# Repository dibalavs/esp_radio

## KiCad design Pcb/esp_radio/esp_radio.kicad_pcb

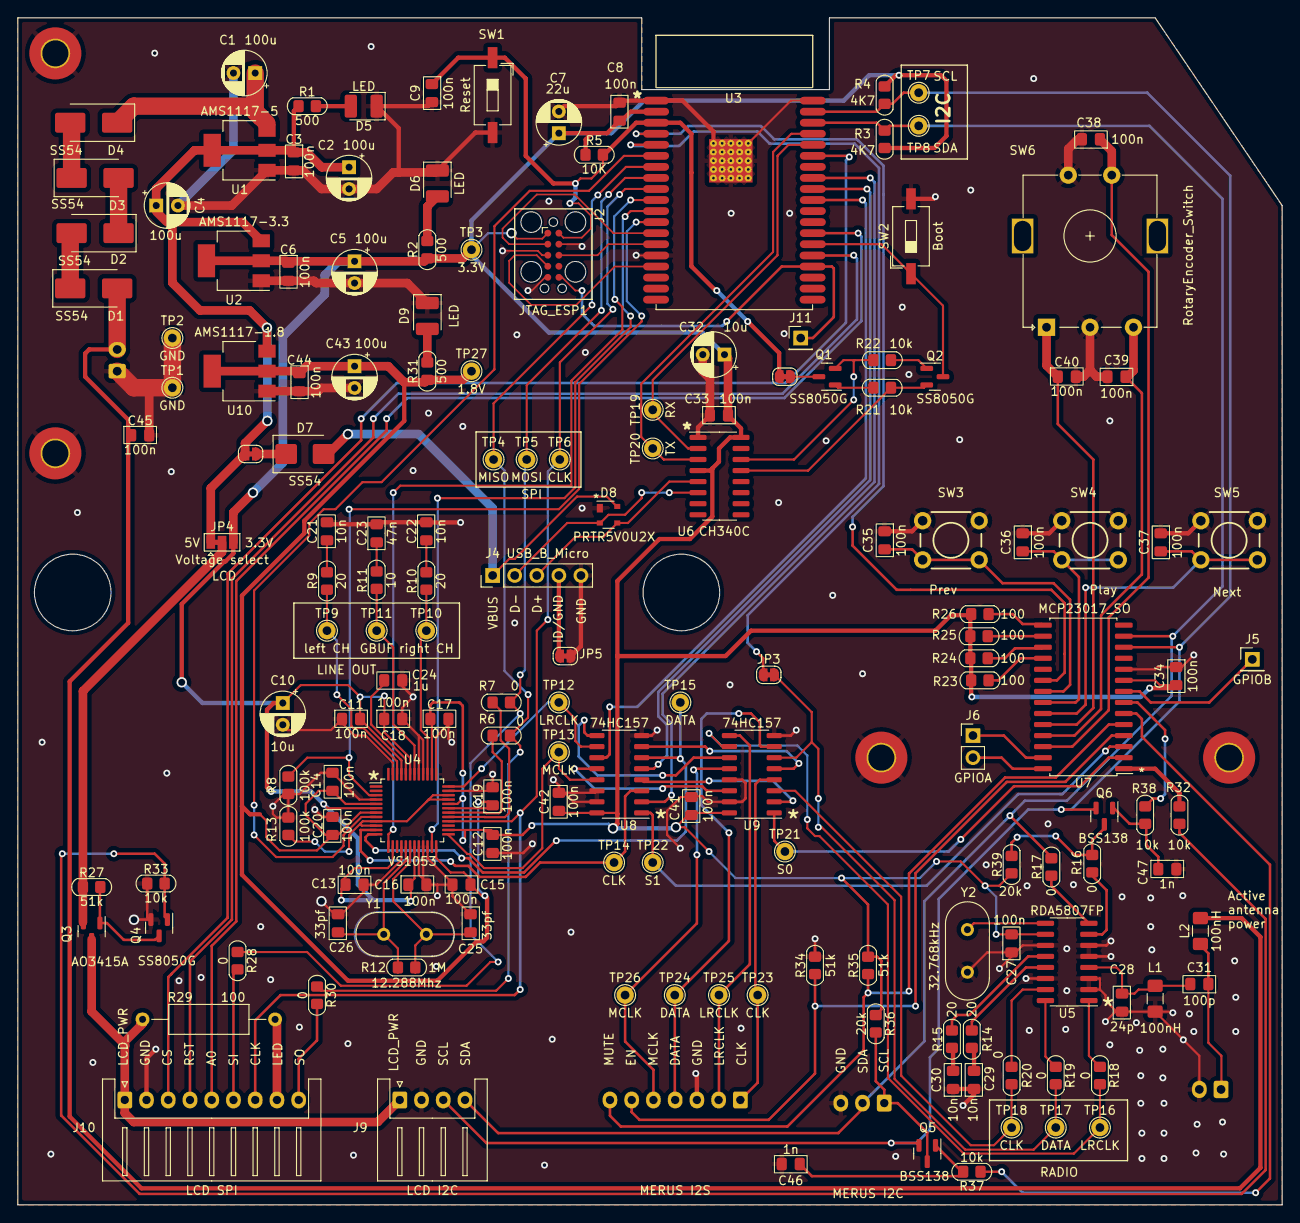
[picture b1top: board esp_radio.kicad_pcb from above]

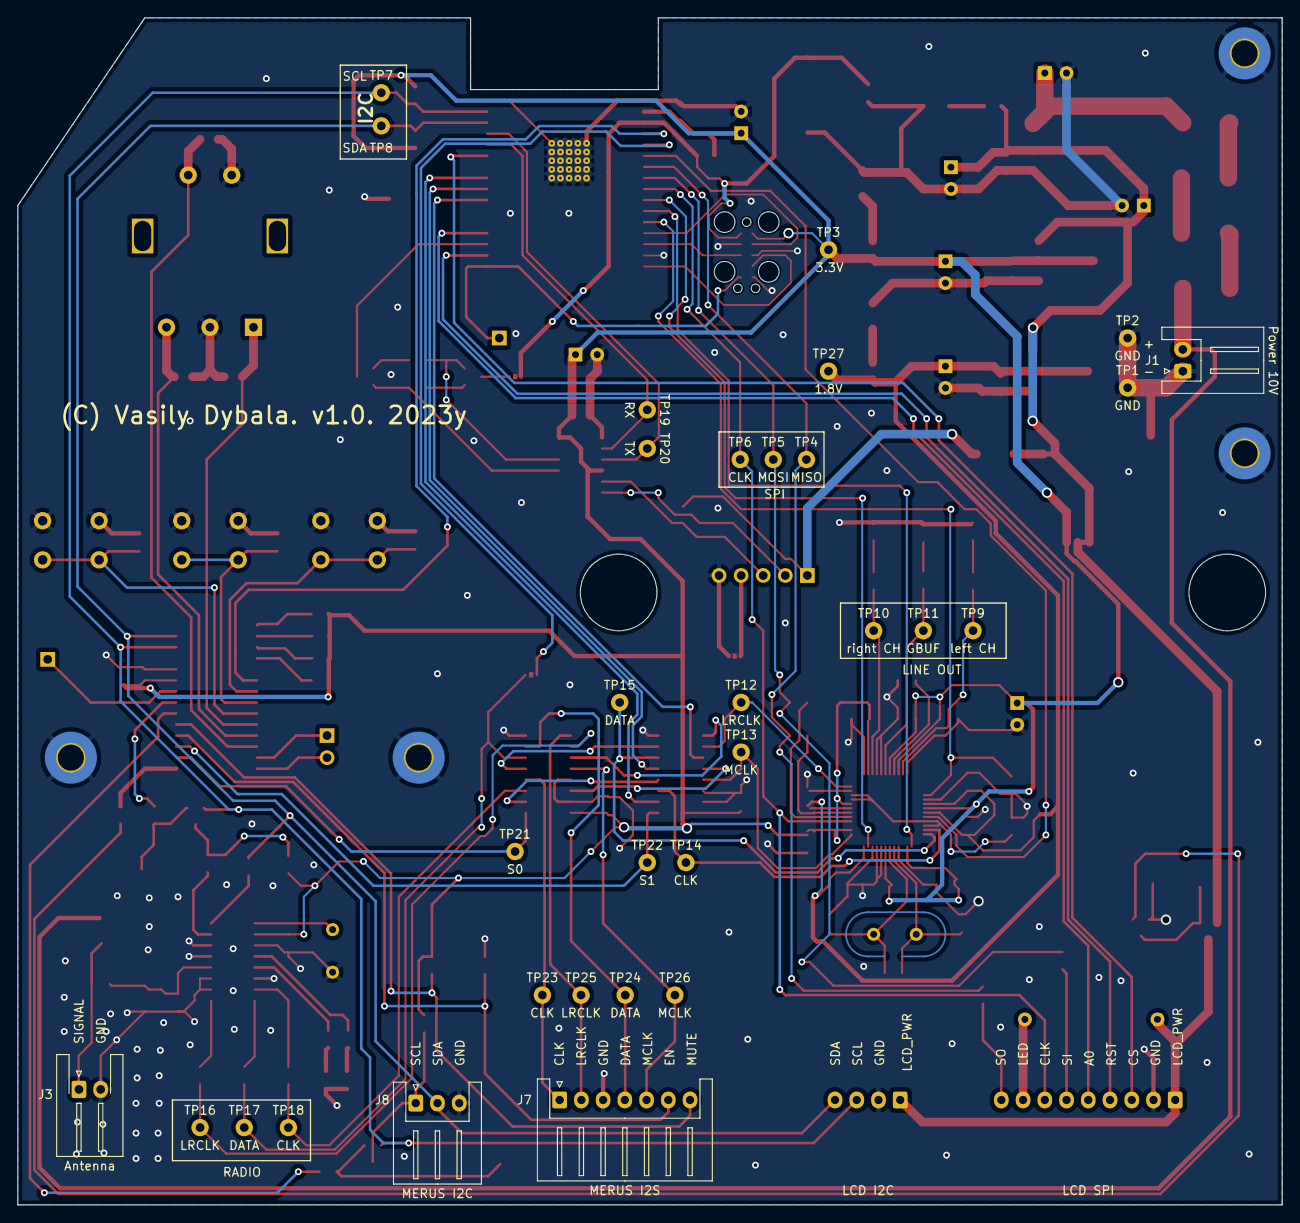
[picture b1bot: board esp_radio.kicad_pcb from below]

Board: 2 copper layers, 145.4 x 136.5 mm, 164 parts (4 on the bottom side), 117 nets.

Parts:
C1, C2, C4, C5, C43: 100u; CP_Radial_D5.0mm_P2.50mm
C3, C6, C8, C9, C11, C12, C13, C14, C15, C16, C17, C18, C19, C20, C27, C33, C34, C35, C36, C37, C38, C39, C40, C41, C42, C44, C45: 100n; C_0805
C7: 22u; CP_Radial_D5.0mm_P2.50mm
C10, C32: 10u; CP_Radial_D5.0mm_P2.50mm
C21, C22, C29, C30: 10n; C_0805
C23: 47n; C_0805
C24: 1u; C_0805
C25, C26: 33pf; C_0805
C28: 24p; C_0805
C31: 100p; C_0805
C46, C47: 1n; C_0805
D1, D2, D3, D4: SS54; D_SMB_Handsoldering
D5, D6, D9: LED; LED_1210_3225Metric_Pad1.42x2.65mm_HandSolder
D7: SS54; D_SMB
D8: PRTR5V0U2X; SOT-143
J1: Power 10V; JST_XH_S2B-XH-A_1x02_P2.50mm_Horizontal
J2: JTAG_ESP1; Tag-Connect_TC2050-IDC-FP_2x05_P1.27mm_Vertical
J3: Antenna; JST_XH_S2B-XH-A-1_1x02_P2.50mm_Horizontal
J4: USB_B_Micro; PinHeader_1x05_P2.54mm_Vertical
J5: GPIOB; PinHeader_1x01_P2.54mm_Vertical
J6: GPIOA; PinHeader_1x02_P2.54mm_Vertical
J7: MERUS I2S; JST_XH_S7B-XH-A_1x07_P2.50mm_Horizontal
J8: MERUS I2C; JST_XH_S3B-XH-A_1x03_P2.50mm_Horizontal
J9: LCD I2C; JST_XH_S4B-XH-A_1x04_P2.50mm_Horizontal
J10: LCD SPI; JST_XH_S9B-XH-A_1x09_P2.50mm_Horizontal
J11: IR; PinHeader_1x01_P2.54mm_Vertical
JP1, JP2, JP3, JP5: SolderJumper_2_Bridged; SolderJumper-2_P1.3mm_Bridged_RoundedPad1.0x1.5mm
JP4: Voltage select; SolderJumper-3_P1.3mm_Bridged12_Pad1.0x1.5mm
L1, L2: 100nH; L_1206_3216Metric_Pad1.42x1.75mm_HandSolder
Q1, Q2, Q4: SS8050G; SOT-23
Q3: AO3415A; SOT-23
Q5, Q6: BSS138; SOT-23
R1, R2, R31: 500; R_0805
R3, R4: 4K7; R_0805
R5: 10K; R_0805
R6, R7, R16, R17, R18, R19, R20, R28, R30: 0; R_0805
R8, R13: 100k; R_0805
R9, R10, R14, R15: 20; R_0805
R11: 10; R_0805
R12: 1M; R_0805
R21, R22, R32, R33, R37, R38: 10k; R_0805
R23, R24, R25, R26: 100; R_0805
R27, R34, R35: 51k; R_0805
R29: 100; R_Axial_DIN0309_L9.0mm_D3.2mm_P15.24mm_Horizontal
R36, R39: 20k; R_0805
SW1: Reset; SW_DIP_SPSTx01_Slide_6.7x4.1mm_W8.61mm_P2.54mm_LowProfile
SW2: Boot; SW_DIP_SPSTx01_Slide_6.7x4.1mm_W8.61mm_P2.54mm_LowProfile
SW3: Prev; SW_PUSH_6mm_H12mm
SW4: Play; SW_PUSH_6mm_H12mm
SW5: Next; SW_PUSH_6mm_H12mm
SW6: RotaryEncoder_Switch; RotaryEncoder_EC16-Switch_Vertical_H20mm
TP1, TP2: GND; TestPoint_THTPad_D2.0mm_Drill1.0mm
TP3: 3.3V; TestPoint_THTPad_D2.0mm_Drill1.0mm
TP4: MISO; TestPoint_THTPad_D2.0mm_Drill1.0mm
TP5: MOSI; TestPoint_THTPad_D2.0mm_Drill1.0mm
TP6, TP14, TP18, TP23: CLK; TestPoint_THTPad_D2.0mm_Drill1.0mm
TP7: SCL; TestPoint_THTPad_D2.0mm_Drill1.0mm
TP8: SDA; TestPoint_THTPad_D2.0mm_Drill1.0mm
TP9: left CH; TestPoint_THTPad_D2.0mm_Drill1.0mm
TP10: right CH; TestPoint_THTPad_D2.0mm_Drill1.0mm
TP11: GBUF; TestPoint_THTPad_D2.0mm_Drill1.0mm
TP12, TP16, TP25: LRCLK; TestPoint_THTPad_D2.0mm_Drill1.0mm
TP13, TP26: MCLK; TestPoint_THTPad_D2.0mm_Drill1.0mm
TP15, TP17, TP24: DATA; TestPoint_THTPad_D2.0mm_Drill1.0mm
TP19: RX; TestPoint_THTPad_D2.0mm_Drill1.0mm
TP20: TX; TestPoint_THTPad_D2.0mm_Drill1.0mm
TP21: S0; TestPoint_THTPad_D2.0mm_Drill1.0mm
TP22: S1; TestPoint_THTPad_D2.0mm_Drill1.0mm
TP27: 1.8V; TestPoint_THTPad_D2.0mm_Drill1.0mm
U1: AMS1117-5; SOT-223-3_TabPin2
U2: AMS1117-3.3; SOT-223-3_TabPin2
U3: ESP32-WROVER_IE; ESP32-WROVER
U4: VS1053; LQFP-48_7x7mm_P0.5mm
U5: RDA5807FP; SOP-16_3.9x9.9mm_P1.27mm
U6: CH340C; SOIC-16_3.9x9.9mm_P1.27mm
U7: MCP23017_SO; SOIC-28W_7.5x17.9mm_P1.27mm
U8, U9: 74HC157; SO-16_3.9x9.9mm_P1.27mm
U10: AMS1117-1.8; SOT-223-3_TabPin2
Y1: 12.288Mhz; Crystal_HC18-U_Vertical
Y2: 32.768kHz; Crystal_HC18-U_Vertical

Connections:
+1V8: C14.2, C15.2, C19.1, C20.1, C43.1, C44.1, R31.1, TP27.1, U4.5 (CVDD), U4.7 (CVDD), U4.24 (CVDD), U4.31 (CVDD), U10.2 (VO)
+3.3V: C5.1, C6.1, C7.1, C8.1, C10.1, C11.2, C12.2, C13.2, C16.1, C17.1, C18.1, C27.2, C32.1, C33.2, C34.2, C41.1, C42.1, J2.1 (VTref), JP4.3 (B), R2.1, R3.1, R4.1, R5.1, R23.1, R24.1, R25.1, R26.1, R35.2, R36.1, R39.1, TP3.1, U2.2 (VO), U3.2 (3V3), U4.6 (IOVDD), U4.14 (IOVDD), U4.19 (IOVDD), U4.26 (RX), U4.32 (~XTEST), U4.38 (AVDD), U4.43 (AVDD), U4.45 (AVDD), U5.10 (VDD), U6.4 (V3), U6.16 (VCC), U7.9 (VDD), U8.16 (VCC), U9.16 (VCC)
+5V: C2.1, C3.1, C4.1, JP1.2 (B), JP4.1 (A), R1.1, U1.2 (VO), U2.3 (VI), U10.3 (VI)
+10V: C45.1, D1.2 (A), J1.2, L2.2
/Audio Decoder/I2S.CLK: TP14.1, U4.11 (I2S_SCLK), U8.3 (1|1)
/Audio Decoder/I2S.DATA: TP15.1, U4.12 (I2S_SDATA), U8.6 (2|1)
/Audio Decoder/I2S.LRCLK: TP12.1, U4.36 (I2S_LROUT), U8.10 (3|1)
/Audio Decoder/I2S.MCLK: TP13.1, U4.25 (I2S_MCLK), U8.13 (4|1)
/Audio Decoder/SPI.CLK: J10.7, TP6.1, U3.9 (IO33), U4.28 (SCLK)
/Audio Decoder/SPI.MISO: R6.1, R30.1, TP4.1, U3.7 (IO35)
/Audio Decoder/SPI.MOSI: R7.1, R28.1, TP5.1, U3.8 (IO32)
/Audio Decoder/VS1053.DREQ: U3.6 (IO34), U4.8 (DREQ)
/Audio Decoder/VS1053.RST: R8.1, U3.12 (IO27), U4.3 (~XRESET)
/Audio Decoder/VS1053.XCS: U3.11 (IO26), U4.23 (XCS)
/Audio Decoder/VS1053.XDCS: U3.10 (IO25), U4.13 (~XDCS)
/ESP_board/FM_ST_INT: JP3.1 (A), U3.5 (IO39)
/ESP_board/I2C.SCL: J9.3, Q5.2 (S), Q6.2 (S), R4.2, TP7.1, U3.37 (IO23), U7.12 (SCK)
/ESP_board/I2C.SDA: J8.2, J9.4, R3.2, R17.1, TP8.1, U3.36 (IO22), U7.13 (SDA)
/ESP_board/I2S0.CLK: U3.31 (IO19), U8.2 (1|0)
/ESP_board/I2S0.DATA: U3.30 (IO18), U8.5 (2|0)
/ESP_board/I2S0.LRCLK: U3.29 (IO5), U8.11 (3|0)
/ESP_board/JTAG.RESET: C9.1, J2.10 (~RESET), JP2.1 (A), R5.2, SW1.1, U3.3 (EN)
/ESP_board/JTAG.TCK: J2.4 (SWDCLK/TCK), U3.16 (TCK)
/ESP_board/JTAG.TDI: J2.8 (NC/TDI), U3.14 (TDI)
/ESP_board/JTAG.TDO: J2.6 (SWO/TDO), J11.1, U3.23 (TDO)
/ESP_board/JTAG.TMS: J2.2 (SWDIO/TMS), U3.13 (TMS)
/ESP_board/LCD.A0: J10.5, U3.26 (IO4)
/ESP_board/LCD.CS: J10.3, U3.33 (IO21)
/ESP_board/LCD.RST: J10.4, U3.24 (IO2)
/ESP_board/UART.BOOT: Q2.3 (C), SW2.1, U3.25 (IO0)
/ESP_board/UART.EN: JP2.2 (B), Q1.3 (C)
/ESP_board/UART.RX: TP19.1, U3.34 (RXD0), U6.2 (TXD)
/ESP_board/UART.TX: TP20.1, U3.35 (TXD0), U6.3 (RXD)
/FM Radio/FmChipSelect: R38.1, U7.7 (GPB6)
/FM Radio/I2S.CLK: R20.2, TP18.1, U9.3 (1|1)
/FM Radio/I2S.DATA: JP3.2 (B), R19.2, TP17.1, U9.6 (2|1)
/FM Radio/I2S.LRCLK: R18.2, TP16.1, U9.10 (3|1)
/I2S Switch/74HC.S0: TP21.1, U7.2 (GPB1), U9.1 (S)
/I2S Switch/74HC.S1: TP22.1, U7.3 (GPB2), U8.1 (S)
/I2S Switch/I2SOUT.CLK: J7.1, TP23.1, U9.4 (1Y)
/I2S Switch/I2SOUT.DATA: J7.4, TP24.1, U9.7 (2Y)
/I2S Switch/I2SOUT.LRCLK: J7.2, TP25.1, U9.9 (3Y)
/I2S Switch/I2SOUT.MCLK: J7.5, TP26.1, U9.12 (4Y)
/IO Expander/INT_EXPANDER: U3.4 (IO36), U7.20 (INTA)
/IO Expander/MERUS.EN: J7.6, R34.1, U7.4 (GPB3)
/IO Expander/MERUS.MUTE: J7.7, R35.1, U7.5 (GPB4)
/IO Expander/MerusChipSelect: R37.1, U7.6 (GPB5)
/LCD screen/LCD.LED: J10.8, R29.2
/LCD screen/LCD_POWER: R32.1, U7.1 (GPB0)
/LCD screen/LCD_PWR: J9.1, J10.1, Q3.3 (D), R29.1
/UART/USB_DN: D8.2 (I/O1), J4.2 (D-), U6.6 (UD-)
/UART/USB_DP: D8.3 (I/O2), J4.3 (D+), U6.5 (UD+)
GND: C1.2, C2.2, C3.2, C4.2, C5.2, C6.2, C7.2, C8.2, C9.2, C10.2, C11.1, C12.1, C13.1, C14.1, C15.1, C16.2, C17.2, C18.2, C19.2, C20.2, C21.2, C22.2, C23.2, C24.1, C25.1, C26.2, C27.1, C28.1, C29.1, C30.1, C32.2, C33.1, C34.1, C35.1, C36.1, C37.1, C38.2, C39.2, C40.2, C41.2, C42.2, C43.2, C44.2, C45.2, C46.2, C47.2, D5.1 (K), D6.1 (K), D8.1 (GND), D9.1 (K), J1.1, J2.3 (GND), J2.5 (GND), J2.9 (GNDDetect), J3.2, J4.5 (GND), J7.3, J8.3, J9.2, J10.2, JP5.1 (A), L1.2, Q4.2 (E), R8.2, R13.1, R33.1, R34.2, SW1.2, SW2.2, SW3.2, SW4.2, SW5.2, SW6.C, SW6.S1, TP1.1, TP2.1, U1.1 (GND), U2.1 (GND), U3.1 (GND), U3.15 (GND), U3.38 (GND), U3.39 (GND), U4.4 (DGND), U4.16 (DGND), U4.20 (DGND), U4.21 (DGND), U4.22 (DGND), U4.35 (DGND), U4.37 (AGND), U4.40 (AGND), U4.41 (AGND), U4.47 (AGND), U5.2 (GND), U5.3 (RF_GND), U5.5 (GND), U5.6 (GND), U5.11 (GND), U5.14 (GND), U6.1 (GND), U7.10 (VSS), U8.8 (GND), U8.14 (4|0), U8.15 (~E), U9.8 (GND), U9.13 (4|1), U9.15 (~E), U10.1 (GND), Y2.1
unnamed: C21.1, R9.2
unnamed: C22.1, R10.2
unnamed: C23.1, R11.2
unnamed: C29.2, R14.2
unnamed: C30.2, R15.2
unnamed: D1.1 (K), D2.2 (A)
unnamed: D2.1 (K), D3.2 (A)
unnamed: D3.1 (K), D4.2 (A)
unnamed: C1.1, D4.1 (K), U1.3 (VI)
unnamed: D5.2 (A), R1.2
unnamed: D6.2 (A), R2.2
unnamed: D7.2 (A), D8.4 (VCC), J4.1 (VBUS)
unnamed: D9.2 (A), R31.2
unnamed: C31.1, J3.1, L2.1
unnamed: J4.4 (ID), JP5.2 (B)
unnamed: J5.1, U7.8 (GPB7)
unnamed: J6.1, U7.27 (GPA6)
unnamed: J6.2, U7.28 (GPA7)
unnamed: J8.1, Q5.3 (D), R36.2
unnamed: J10.6, R28.2
unnamed: J10.9, R30.2
unnamed: JP4.2 (C), Q3.2 (S), R27.1
unnamed: Q1.1 (B), R21.2
unnamed: Q1.2 (E), R22.1, U6.14 (~RTS)
unnamed: Q2.1 (B), R22.2
unnamed: Q2.2 (E), R21.1, U6.13 (~DTR)
unnamed: Q3.1 (G), Q4.3 (C), R27.2
unnamed: Q4.1 (B), R32.2, R33.2
unnamed: C46.1, Q5.1 (G), R37.2
unnamed: Q6.3 (D), R16.1, R39.2
unnamed: C47.1, Q6.1 (G), R38.2
unnamed: R11.1, TP11.1, U4.42 (GBUF)
unnamed: R13.2, U4.9 (GPIO2), U4.10 (GPIO3), U4.33 (GPIO0), U4.34 (GPIO1)
unnamed: R9.1, TP9.1, U4.46 (LEFT)
unnamed: C24.2, U4.44 (RCAP)
unnamed: R10.1, TP10.1, U4.39 (RIGHT)
unnamed: R7.2, U4.29 (SI)
unnamed: R6.2, U4.30 (SO)
unnamed: C25.2, R12.1, U4.18 (XTALI), Y1.2
unnamed: C26.1, R12.2, U4.17 (XTALO), Y1.1
unnamed: C28.2, C31.2, L1.1, U5.4 (FMIN)
unnamed: R18.1, U5.1 (I2S_LROUT)
unnamed: R19.1, U5.16 (I2S_DATA/ST_INT)
unnamed: R20.1, U5.15 (I2S_SCLK)
unnamed: R14.1, U5.13 (LOUT)
unnamed: U5.9 (RCLK), Y2.2
unnamed: R15.1, U5.12 (ROUT)
unnamed: R16.2, U5.7 (SCLK)
unnamed: R17.2, U5.8 (SDA)
unnamed: R26.2, U7.15 (A0)
unnamed: R25.2, U7.16 (A1)
unnamed: R24.2, U7.17 (A2)
unnamed: C35.2, SW3.1, U7.21 (GPA0)
unnamed: C36.2, SW4.1, U7.22 (GPA1)
unnamed: C37.2, SW5.1, U7.23 (GPA2)
unnamed: C40.1, SW6.A, U7.24 (GPA3)
unnamed: C39.1, SW6.B, U7.25 (GPA4)
unnamed: C38.1, SW6.S2, U7.26 (GPA5)
unnamed: R23.2, U7.18 (~RESET)
unnamed: U8.4 (1Y), U9.2 (1|0)
unnamed: U8.7 (2Y), U9.5 (2|0)
unnamed: U8.9 (3Y), U9.11 (3|0)
unnamed: U8.12 (4Y), U9.14 (4|0)
V_USB: D7.1 (K), JP1.1 (A)

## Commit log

2023-03-08 Initial adding
2023-03-11 Move custom components to kicad_common_library.
2023-03-11 Add new datasheets and board photos
2023-03-21 Add docs.
2023-03-21 Add helper PCB scripts
2023-03-21 Update submodule revision
2023-03-21 Add components layout on PCB
2023-03-27 Partially route board
2023-04-02 Additional routing
2023-04-11 Finish board routing
2023-04-11 Initial adding KaRadio project as base firmware
2023-04-11 Add ST7567S dstasheet
2023-04-12 Add bus initialization to separate bus.c file
2023-04-12 Remove unused xpt2046 driver
2023-04-12 Global refactoring. part 1.
    Add component prefix to function names and use snake_case_notation.
2023-04-12 Global refactoring. Part 2
2023-04-12 Global refactoring. Part 3.
2023-04-12 Rename app_main4.h to app_main.c
2023-04-13 Fix ucg/u8g2 includes.
2023-04-14 Re-write button handling code.
    Now we use i2c expander mcp23017 to handle keys and encoder.
2023-04-22 Remove unused code
2023-04-22 Add chip select emulation for i2c devices
2023-04-22 Add checklist to check PCB
2023-04-22 Update submodule hash
2023-04-22 Export gerber file.
2023-05-07 Initial adding RDA5807 FM radio chip.
2023-05-07 MerusAudio: Remove unused include/src.
2023-05-07 ext_gpio: Add chip select emulation for RDA and Merus.
2023-05-11 keyboard. Fix rotary encoder and keyboard.
2023-05-14 Add task to show status of tasks and CPU and stack usage.
2023-05-14 Disable ota task
2023-05-16 Move wifi initialization to separate file.
2023-06-12 Add i2s redirector.
    Convertor which can convert i2s stream to be compatible
    with MerusAudio format.
2023-06-12 Pcb. Fix hw issues.
    Add loop to esp32 after i2s switcher
    esp32 can convert stream to format compatible to MerusAudio.
2023-06-12 Remove unused function from gpio.c
2023-06-12 Add coreId to debug info task.
2023-06-12 Fix gpio36 extra interrupts.
2023-06-12 vs1053: Extract mclk and speed to separate functions
2023-06-12 mcp23017: Use native i2c API instead of custom bus impl.
2023-06-12 bus.c: Add i2s in/out initialization. Switch to legacy i2s api.
2023-06-12 merus: Disable i2s during communication on i2c.
2023-06-12 MerusAudio: Add initialization of i2s format.
2023-06-12 addon: Fix click condition checking.
2023-06-12 main: Refactor wi-fi initialization.
    Now it is async.
2023-06-12 audio_renderer: Add hardcode initialization
2023-06-12 ntp: Try to sync ntp only if network is available
2023-06-13 Update submodules. Add esp-idf submodule.
2023-06-13 Introduce app_state and kmalloc wrapper
2023-06-14 Introduce action_manager. Implement volume control over manager.
2023-06-17 Move station control to action manager.
2023-06-17 Fix I2S format used by MA12070p
2023-06-17 Fix rotary encoder stability.
2023-06-18 Add special function to stop/start I2S stream.
2023-06-18 Fix non-working start/stop button.
2023-06-19 Rewrite SPIRAM fifo to FreeRTOR's streambuffer.
2023-06-19 Fix debug stats task to layout core column.
2023-06-20 vs1053: Use interrupts instead of polling.
    Reduce cpu usage from 92% to 1%.
2023-06-20 vs1053: Disable patch. to speedup initialization.
2023-06-22 Use helper macro to ptotect SPI transaction with lock.
2023-06-23 app_state: Automatic saving settings by timeout.
2023-06-29 Add current playing device facade.
2023-07-01 Use NVS storage to store common settings.
2023-07-01 Add manual about web streaming.
2023-07-04 Move hw initialization to action manager.
2023-07-05 Add Web page infrastructure
2023-07-07 Implement player component on web page
2023-07-07 Allow to load .gz-ipped files
2023-08-17 Add web pages.
2023-09-07 Implement new webserver.
2023-09-23 Add VS1053 settnigs
2023-11-26 Update mdns component.
2023-11-26 Update web page.
2023-11-26 Update components hashes
2023-11-26 Add script to convert I2S stream to .wav file
2023-11-26 Update submodue hashes.
2023-11-26 Add some logs and comments to components.
2023-11-26 app_main fixes.
    - Enable UART task
    - add echo to UART to work with idf monitor
    - switch to SW mp3 decoder
    - Show content of SPIFFS image
2023-11-26 Fix some bugs
2023-11-26 fix I2S parameters.
2023-11-26 Fix webserver bugs.
2023-11-26 Allow to change samplerate via UART cli
2023-11-26 vs1053 set default volume on init
2023-11-26 webclient: Fix path part of URL
2023-11-26 config: Enable VFS in config
2023-11-26 Allow to stop i2s_redirector on SW decoding
2023-12-11 Migrate to new I2S API
